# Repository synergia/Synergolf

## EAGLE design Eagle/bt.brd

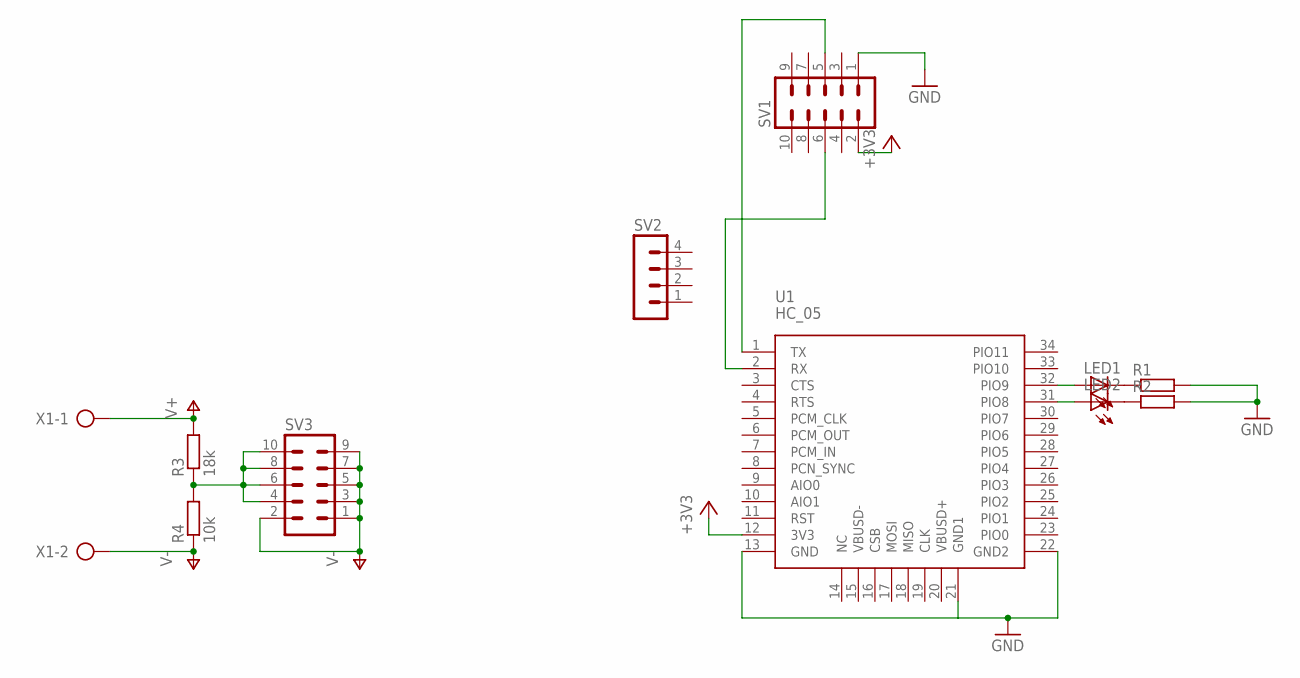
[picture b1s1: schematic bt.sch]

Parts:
LED1, LED2: LED3MM
R1, R2: R-EU_R0805; R0805
R3: 18k; R0805
R4: 10k; R0805
SV1, SV3: ML10
SV2: MA04-1
U1: HC_05; BLUETOOTH_SMD
X1: AK500/2

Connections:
+3V3: SV1.2, U1.12 (3V3)
GND: R1.2, R2.2, SV1.1, U1.13 (GND), U1.21 (GND1), U1.22 (GND2)
unnamed: SV1.5, U1.1 (TX)
unnamed: SV1.6, U1.2 (RX)
unnamed: LED1.K (C), R1.1
unnamed: LED2.K (C), R2.1
unnamed: LED2.A, U1.31 (PIO8)
unnamed: LED1.A, U1.32 (PIO9)
unnamed: R3.1, R4.2, SV3.4, SV3.6, SV3.8, SV3.10
V+: R3.2, X1.1
V-: R4.1, SV3.1, SV3.2, SV3.3, SV3.5, SV3.7, SV3.9, X1.2

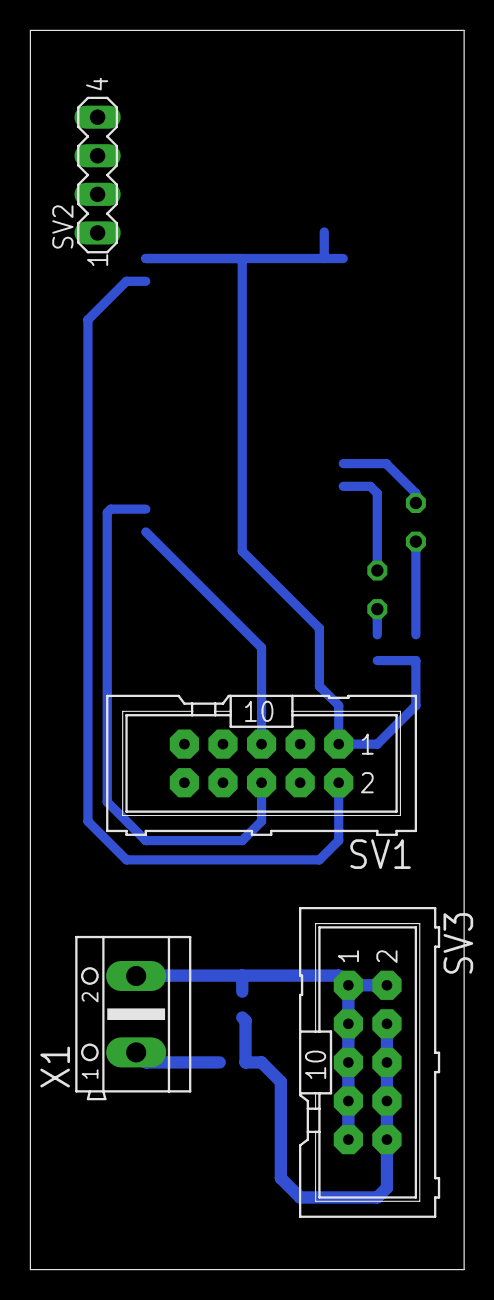
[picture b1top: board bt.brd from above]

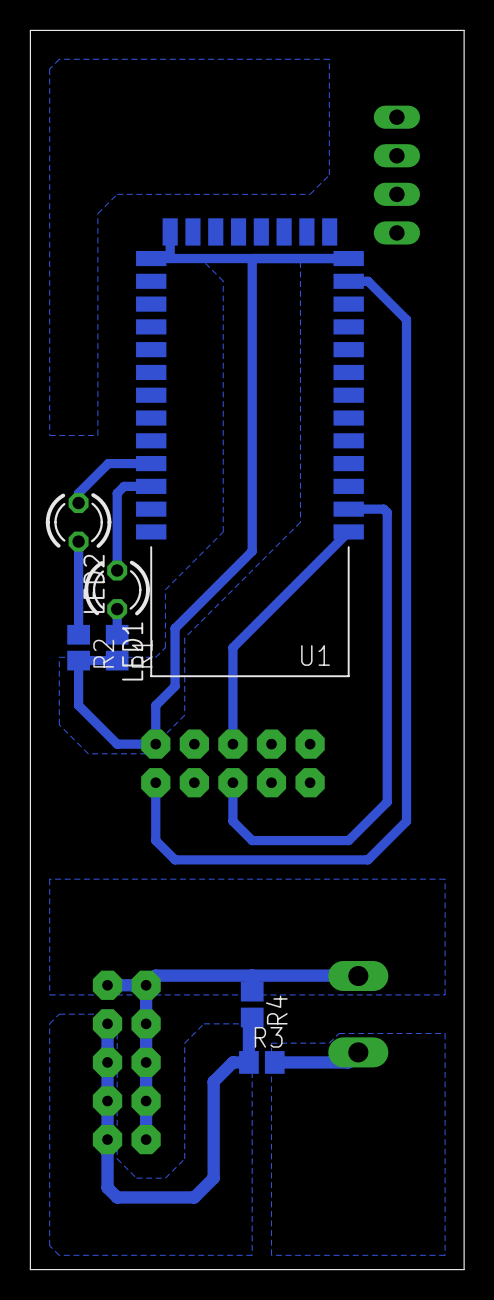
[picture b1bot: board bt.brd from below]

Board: 2 copper layers, 28.6 x 81.6 mm, 11 parts (7 on the bottom side), 11 nets.

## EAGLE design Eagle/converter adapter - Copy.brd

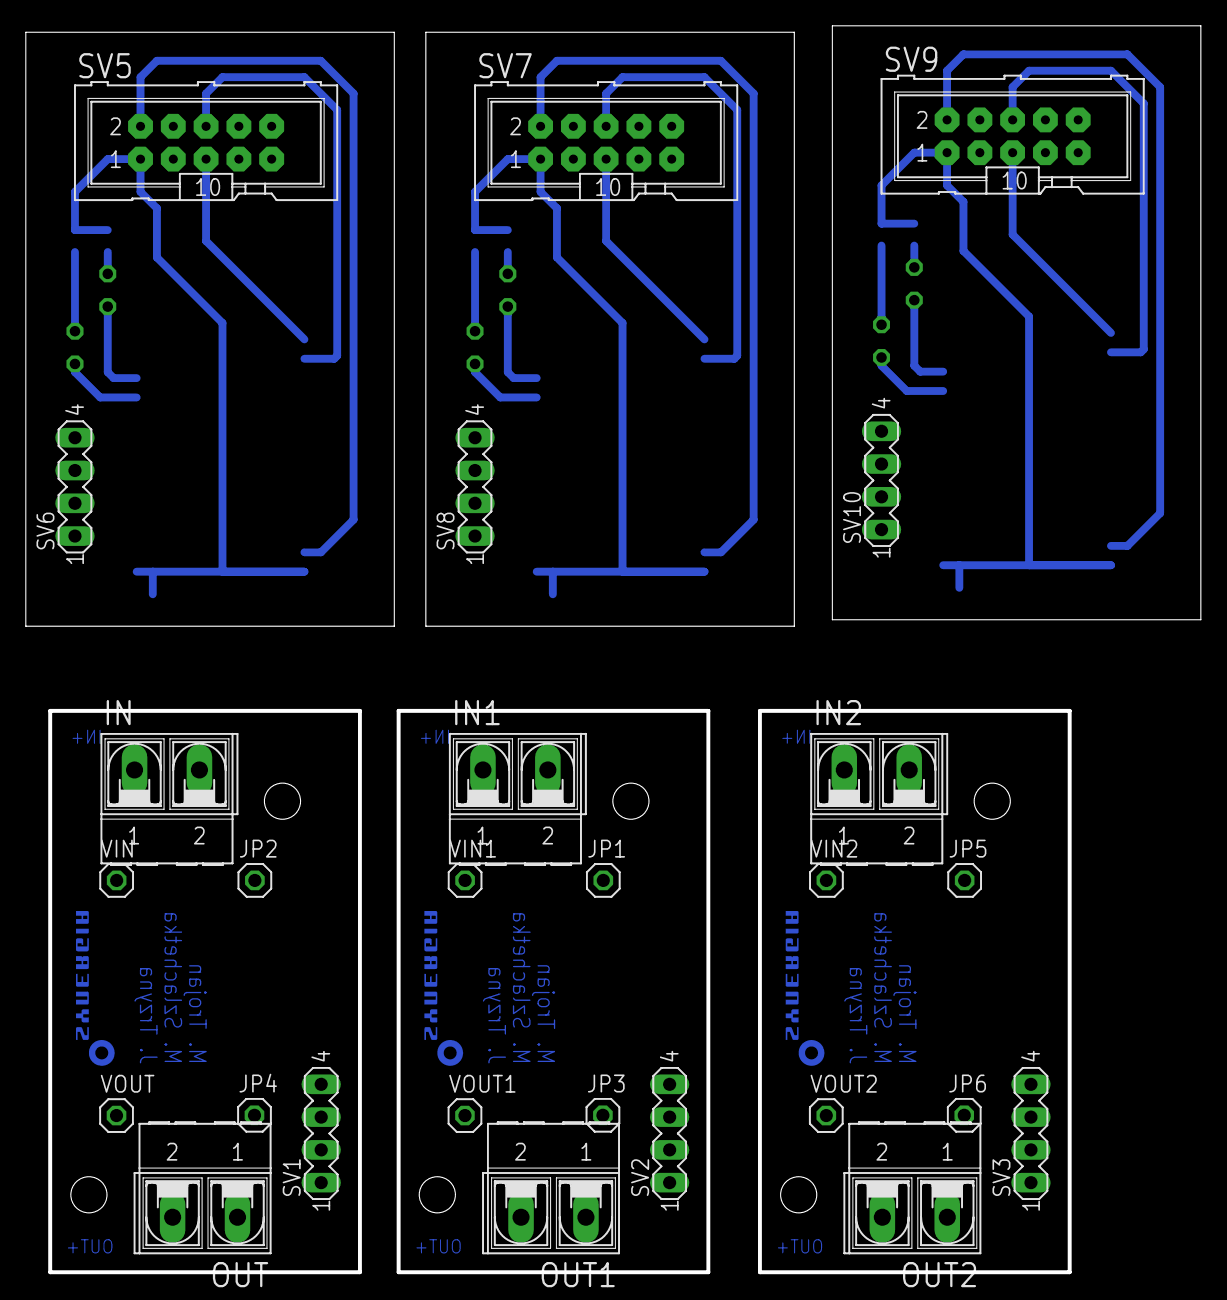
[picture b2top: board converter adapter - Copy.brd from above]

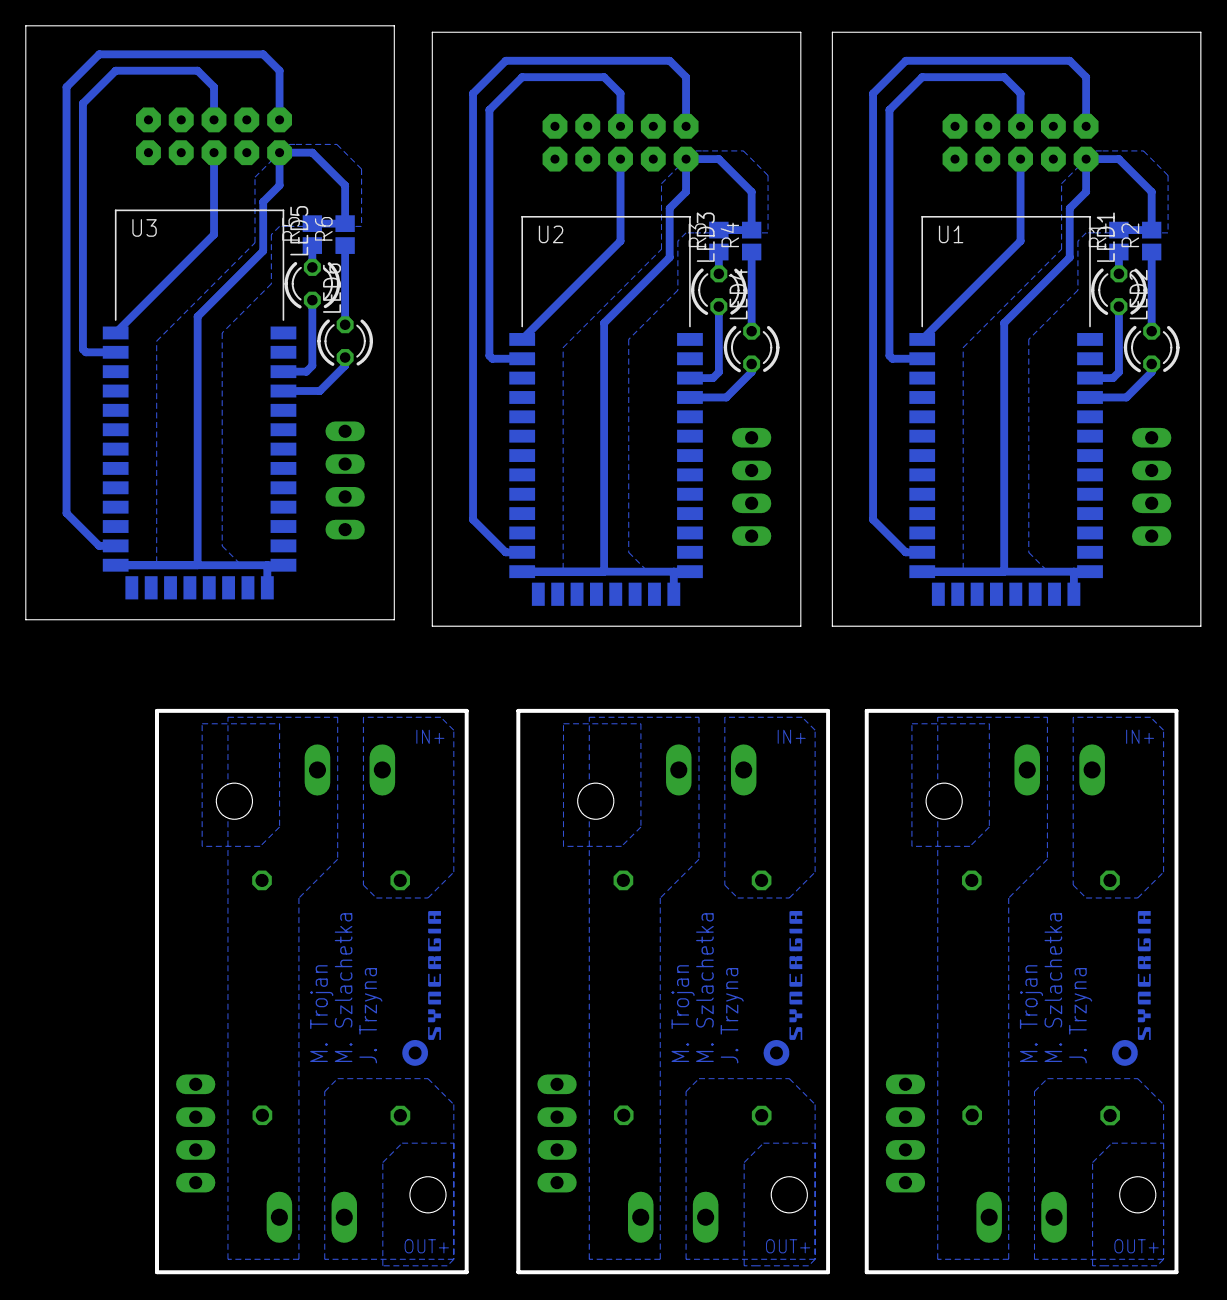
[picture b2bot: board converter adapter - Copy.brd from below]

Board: 2 copper layers, 90.8 x 96.4 mm, 45 parts (18 on the bottom side), 33 nets.

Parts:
IN, IN1, IN2: AK500/2-H
JP1, JP2, JP3, JP4, JP5, JP6: 1X01
LED1, LED2, LED3, LED4, LED5, LED6: LED3MM
OUT, OUT1, OUT2: AK500/2-H
R1, R2, R3, R4, R5, R6: R0805
SV1, SV2, SV3, SV6, SV8, SV10: MA04-1
SV5, SV7, SV9: ML10
U1, U2, U3: HC_05; BLUETOOTH_SMD
U$1, U$2, U$3: SYNERGIA_12MM
VIN, VIN1, VIN2: 1X01
VOUT, VOUT1, VOUT2: 1X01

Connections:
+3V1: SV5.2, U1.12
+3V2: SV7.2, U2.12
+3V3: SV9.2, U3.12
GND: IN.2, JP2.1, JP4.1, OUT.1
GND1: IN1.2, JP1.1, JP3.1, OUT1.1
GND2: IN2.2, JP5.1, JP6.1, OUT2.1
GND4: R1.2, R2.2, SV5.1, U1.13, U1.21, U1.22
GND5: R3.2, R4.2, SV7.1, U2.13, U2.21, U2.22
GND6: R5.2, R6.2, SV9.1, U3.13, U3.21, U3.22
unnamed: OUT.2, VOUT.1
unnamed: IN.1, VIN.1
unnamed: OUT1.2, VOUT1.1
unnamed: IN1.1, VIN1.1
unnamed: OUT2.2, VOUT2.1
unnamed: IN2.1, VIN2.1
unnamed: SV5.5, U1.1
unnamed: SV5.6, U1.2
unnamed: LED2.A, U1.31
unnamed: LED1.A, U1.32
unnamed: LED1.K, R1.1
unnamed: LED2.K, R2.1
unnamed: SV7.5, U2.1
unnamed: SV7.6, U2.2
unnamed: LED4.A, U2.31
unnamed: LED3.A, U2.32
unnamed: LED3.K, R3.1
unnamed: LED4.K, R4.1
unnamed: SV9.5, U3.1
unnamed: SV9.6, U3.2
unnamed: LED6.A, U3.31
unnamed: LED5.A, U3.32
unnamed: LED5.K, R5.1
unnamed: LED6.K, R6.1

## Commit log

2015-05-10 :octocat: Added .gitattributes & .gitignore files
2015-05-10 3DC motors, 1Stepper, Communication
    only adc left
2015-05-13 adc, leds init
2015-05-15 final v1.0
2016-05-13 Smooth putter adjustement. Usart communication improved.
    Quick fixes.
